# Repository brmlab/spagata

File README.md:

spagata
=======

osmocomBB devkit

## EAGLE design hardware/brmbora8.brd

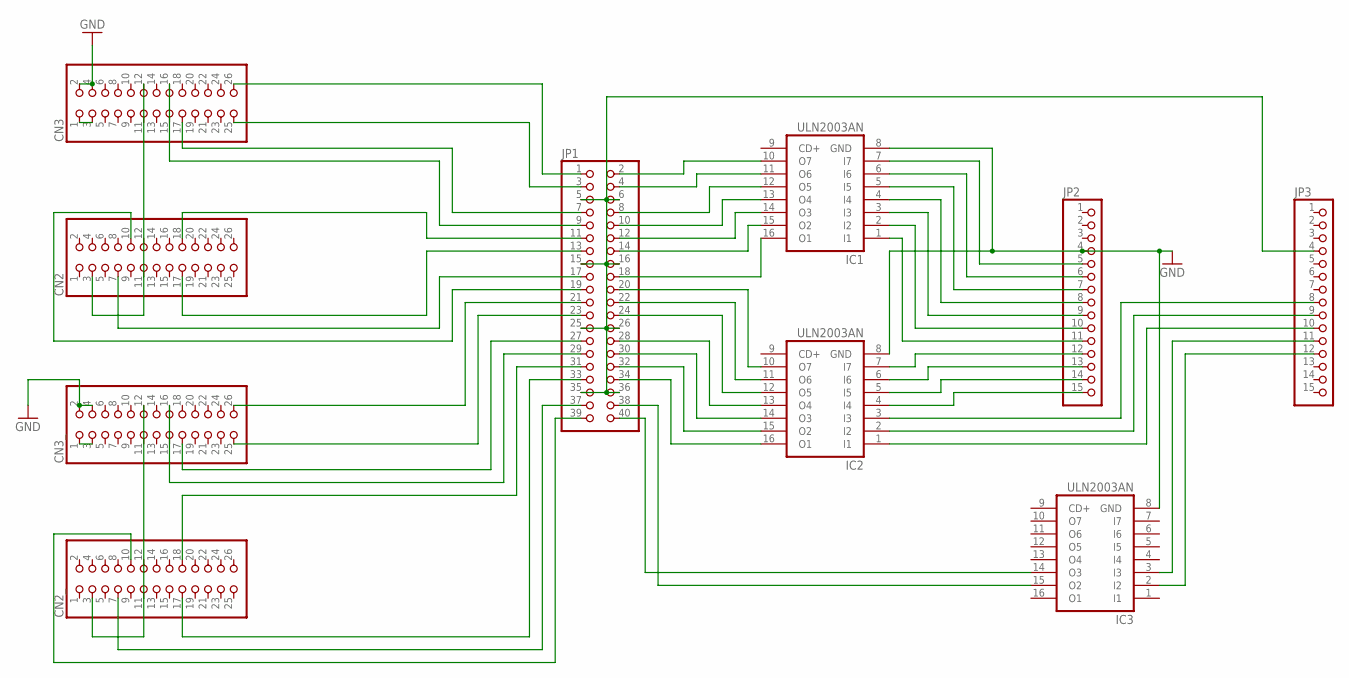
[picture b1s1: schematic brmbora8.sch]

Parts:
CN2, CN2_, CN3, CN3_: PINHD-2X13; 2X13
IC1, IC2, IC3: ULN2003AN; DIL16
JP1: PINHD-2X20-BIG; 2X20-BIG
JP2, JP3: PINHD-1X15; 1X15

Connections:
CN3_: CN3_.1, CN3_.3
GND: CN3.2, CN3.4, CN3_.2, CN3_.4, IC1.8 (GND), IC2.8 (GND), IC3.8 (GND), JP2.4
unnamed: IC1.13 (O4), JP1.10
unnamed: IC1.7 (I7), JP2.5
unnamed: IC1.6 (I6), JP2.6
unnamed: IC1.5 (I5), JP2.7
unnamed: IC1.4 (I4), JP2.8
unnamed: IC1.3 (I3), JP2.9
unnamed: IC1.2 (I2), JP2.10
unnamed: IC1.1 (I1), JP2.11
unnamed: IC2.7 (I7), JP2.12
unnamed: IC2.6 (I6), JP2.13
unnamed: IC2.5 (I5), JP2.14
unnamed: IC2.4 (I4), JP2.15
unnamed: IC2.1 (I1), JP3.10
unnamed: IC2.2 (I2), JP3.9
unnamed: IC2.3 (I3), JP3.8
unnamed: IC3.3 (I3), JP3.11
unnamed: IC3.2 (I2), JP3.12
unnamed: IC3.15 (O2), JP1.38
unnamed: IC3.14 (O3), JP1.40
unnamed: IC2.16 (O1), JP1.34
unnamed: IC2.15 (O2), JP1.32
unnamed: IC2.14 (O3), JP1.30
unnamed: IC2.13 (O4), JP1.28
unnamed: IC2.12 (O5), JP1.24
unnamed: IC2.11 (O6), JP1.22
unnamed: IC2.10 (O7), JP1.20
unnamed: JP1.5, JP1.6, JP1.15, JP1.16, JP1.25, JP1.26, JP1.35, JP1.36, JP3.4
unnamed: IC1.16 (O1), JP1.18
unnamed: IC1.15 (O2), JP1.14
unnamed: IC1.14 (O3), JP1.12
unnamed: IC1.12 (O5), JP1.8
unnamed: IC1.11 (O6), JP1.4
unnamed: IC1.10 (O7), JP1.2
unnamed: CN3.1, CN3.3
unnamed: CN2.3, CN2.11, CN3.12
unnamed: CN3.26, JP1.1
unnamed: CN2_.3, CN2_.11, CN3_.12
unnamed: CN3.25, JP1.3
unnamed: CN2.18, JP1.11
unnamed: CN3.17, JP1.7
unnamed: CN3.16, JP1.9
unnamed: CN2.17, JP1.13
unnamed: CN2.10, JP1.19
unnamed: CN2.7, JP1.17
unnamed: CN3_.26, JP1.21
unnamed: CN3_.25, JP1.23
unnamed: CN3_.16, JP1.29
unnamed: CN3_.17, JP1.27
unnamed: CN2_.18, JP1.31
unnamed: CN2_.17, JP1.33
unnamed: CN2_.10, JP1.39
unnamed: CN2_.7, JP1.37

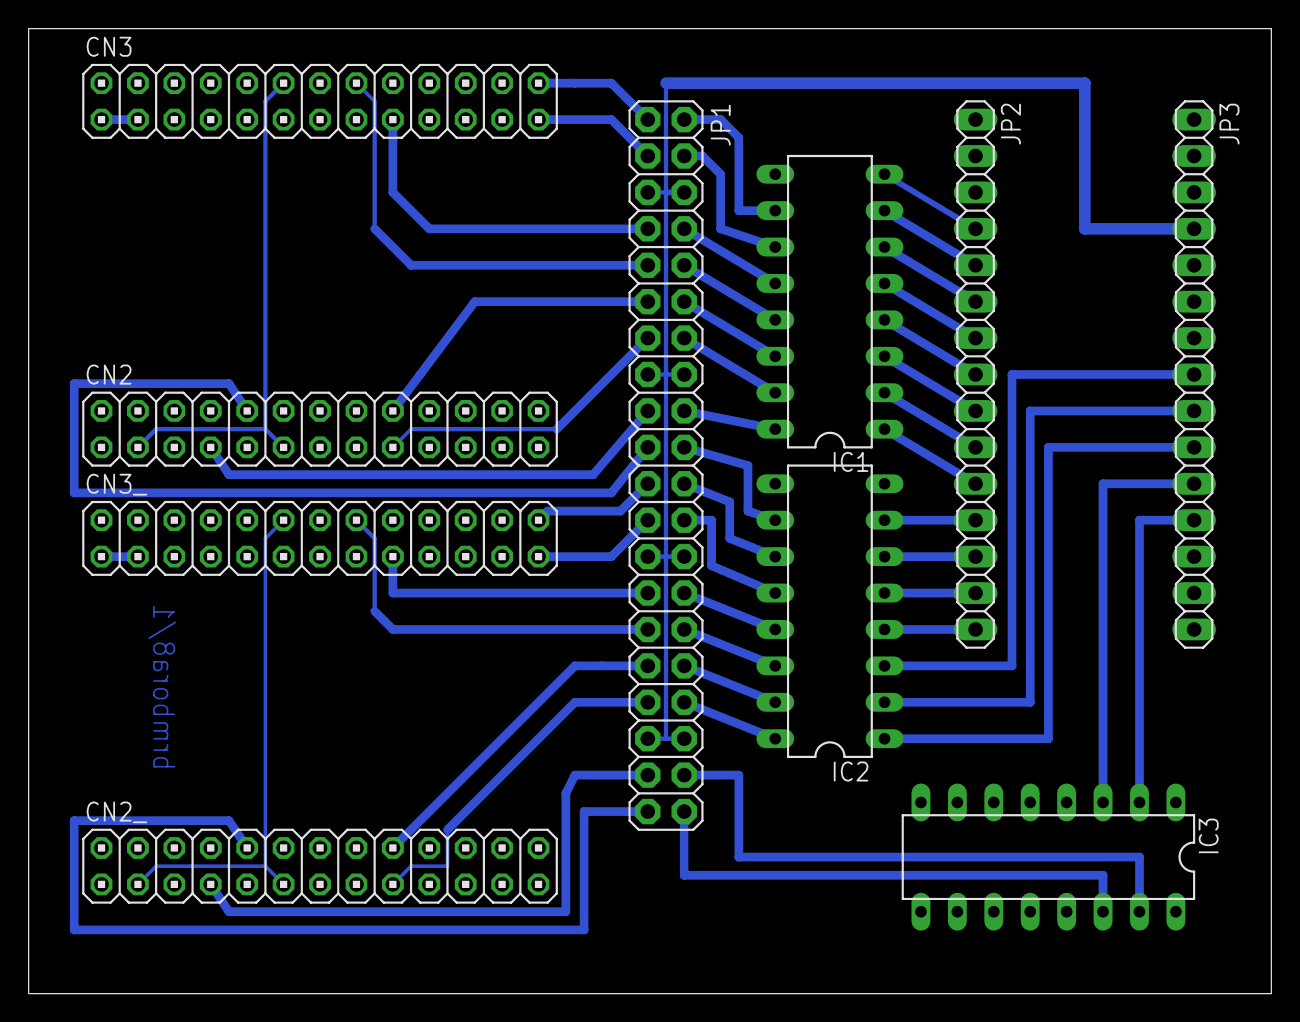
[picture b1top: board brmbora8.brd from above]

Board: 2 copper layers, 86.7 x 67.3 mm, 10 parts (0 on the bottom side), 54 nets.

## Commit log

2012-06-12 Initial commit board v1, firmware for arduino
